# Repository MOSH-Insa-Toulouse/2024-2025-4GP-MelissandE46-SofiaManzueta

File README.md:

# 2024-2025-4GP-MelissandE46-SofiaManzueta

# Projet Capteur

## Sommaire 
*  [Objectifs de ce projet](#objectifs-de-ce-projet)
*  [Déroulé du projet](#diagramme-du-projet)
*  [Simulation du capteur graphite sur LTSpice](#simulation-du-capteur-graphite-sur-ltspice)
*  [Shield PCB sur Kicad](#shield-pcb-sur-kicad)
*  [Code Arduino](#code-arduino)
*  [App Android](#app-android)
*  [La Datasheet](#la-datasheet)

## Objectifs de ce projet

<details>
<summary>  Création d'un capteur de contrainte en graphite  </summary>
   Nous allons utiliser les traces de crayon sur du papier comme une jauge de contrainte pour détecter les déformations en compression et en traction.<br/>
   Les mines de crayon standard sont composées de fines particules de graphite liées entre elles par des liants argileux. Lorsqu'on utilise un crayon, le frottement entre la mine et le papier entraîne le frottement de particules de graphite qui adhèrent aux fibres du papier. Ces traces de crayon peuvent être considérées comme de minces films conducteurs constitués de réseau de particules de graphite percolées sur le papier qui peuvent prendre des formes et des motifs arbitraires. L'expansion et la contraction de ce réseau de particules de graphite, induites par des contraintes mécaniques ou des interactions chimiques, devraient grandement affecter la qualité des contacts interparticulaires et donc le conductivité électrique globale. Il est important de noter que les mines de crayon plus dures contiennent une proportion plus élevée de liants argileux, alors que les mines plus molles contiennent une proportion plus grande de particules de graphite. Ces dernières permettent d'obtenir une résistance de base plus faible qu'avec les mines plus dures. Il a été observé que les variations de résistance moyennes étaient linéairement liées aux amplitudes moyennes de déflexion, avec des écarts d'environ 1%.<br/>
En utilisant la théorie de la percolation, la conductance totale G_{tot} d'un réseau de conducteurs hautement désordonné est :<br/>
   $$G_{tot}=G_0e^{-\xi_c}$$, ici $$\xi_c$$ est la valeur de $$\xi$$ au seuil de percolation qui est le point où un cluster connecté infiniment grand commence à émerger lorsque des paires de nanoparticules voisines choisie au hasard sont connectées par des conducteurs dans un ordre décroissant de valeurs de G<br/>
   If $$-\delta\lambda/2\leq\delta\lambda/2$$,<br/>
   $$\xi_c= \left( {\frac{2f_c\delta\lambda\delta\epsilon}{1-f_v}} \right)^{1/2}+\delta_M-\delta\lambda/2+\epsilon_M-\delta\epsilon/2$$ <br/>
   If $$\delta\lambda/2-\delta\epsilon/2\leq\delta\epsilon/2-\delta\lambda/2$$, <br/>
   $$\xi_c=\lambda_M+\epsilon_M-\left( \frac{1}{2}-\frac{f_c}{1-f_v} \right)\delta\epsilon$$<br/>
   *  $$f_c$$ est la fraction des conducteurs<br/>
   *  $$f_v$$ est la fraction de vide<br/>
   *  $$\lambda_M=L_M\beta$$ et $$E_M=E_{CM}/kT$$ sont les valeurs moyennes des distributions, avec $$L_M$$ l'espace moyen (hors vide) séparant les nanoparticules voisines et $$E_{CM}$$ l'énergie coulombienne de charge moyenne<br/>
   *  $$\delta\lambda$$ et $$\delta\epsilon$$ sont les largeurs des distributions
  
</details>

<details>
<summary>  Réalisation d'un shield PCB pour Arduino UNO  </summary>
   Nous avons créer un shield PCB afin de relier à l'arduino UNO :<br/>  
        *  Un écran OLED  <br/>
        *  Un potentiomètre digital en SPI   <br/>
        *  Un amplificateur transimpédance, lui-même relié au capteur graphite décrit plus haut et au potentiomètre digital  <br/>
        *  Un module Bluetooth  <br/>
        *  Un flex sensor  <br/>
        *  Un encodeur rotatoir auquel on ajoute un déparasite (une capacité entre la clock et le ground)   <br/><br/>

</details>

<details>
<summary>  Création d'un code Arduino  </summary>
Le code crée à l'occasion de ce projet permet de se déplacer dans un menu à l'aide de l'encodeur rotatoire et accéder à différentes fonctions telles que :<br/>
   -La fonction Capteur qui mesure la résistance du capteur graphite, l'affiche sur l'écran OLED et la transmet par bluetooth<br/>
   -La fonction Flex qui mesure la résistance du flex sensor et l'affiche sur l'écran OLED<br/>
   -La fonction Mesure continue qui indique à l'utilisateur la marche à suivre pour réaliser une mesure en continue, que ce soit pour le flex sensor ou le capteur graphite * <br/>
   -La fonction Informations qui renvoie l'utilisateur vers l'application pour Android pour obtenir plus d'informations, l'écran OLED étant très limité<br/>
   -La fonction Creatrices qui indique tout simplement par qui a été réalisé ce projet<br/>

   *Un fil reliant la pin Switch de l'encodeur rotatoire avec le flex sensor a été ajouté. Le but principal est d'agir comme une résistance pull-up pour pouvoir utiliser le bouton switch plus simplement. Cependant, il permet également d'utiliser le flex sensor comme un bouton. En maintenant le flex sensor en compression, on obtient donc des mesures en continue.
   
</details>

<details>
<summary>  Élaboration d'une app Android  </summary>
  Une application a été créée à l'aide de MIT App Inventor (https://appinventor.mit.edu/). Celle-ci permet d'accéder aux mesures réalisées par le capteur graphite, de les afficher dans un graphe et de récupérer ses valeurs dans un fichier. Elle permet également d'obtenir de plus amples informations sur le contexte de ce projet lorsqu'on arrive sur l'écran Informations. Les photos de la partie Designers (ce qui est vu par l'utilisateur) et la partie Blocks (le code derrière l'application) sont disponibles dans le dossier Application Android.
</details>

<details>
<summary>  Rédaction datasheet  </summary>
  Les données de la datasheet proviennent des mesures réalisées avec le code Arduino sur le circuit présenté précédemment. Pour les mines 6B à HB, nous avons mesurer la résistance du capteur graphite pour différentes déformations en tension et en compression. Pour ces déformations, nous avons utilisé des cylindres avec des diamètres de 2cm, 2.5cm, 3cm, 3.5cm, 4cm, 4.5cm et 5cm. Cela nous donne donc des déformations respectivement de 0.1, 0.08, 0.067, 0.057, 0.05, 0.044, 0.04 puisque nous avons mesuré l'épaisseur du capteur e = 0.2cm et que $$\epsilon = \frac{e}{D}$$. On obtient ainsi les courbes caractéristiques suivantes. 

Comme on s'y attendait, en cas de compression, la résistance du capteur graphite diminue lorsque la déformation $$\epsilon$$ augmente. A l'inverse, en cas de tension, la résistance du capteur graphite augmente en fonction de la déformation $$\epsilon$$. Pour ces deux cas de figure, nous pouvons observer que la pente de la courbe est dépendante de la mine utilisée. En effet, la variation relative de résistance est plus élevée pour les mines plus dures, comme cela est décrit dans l'article Pencil Drawn Strain Gauges and Chemiresistors on Paper de Cheng-Wei Lin, Zhibo Zhao, Jaemyung Kim et Jiaxing Huang.

Les résultats du capteur graphite peuvent également être comparés à ceux obtenus avec un flex sensor commercial (celui-ci ne peut être utilisé qu'en tension). Tout d'abord, on peut remarquer que les mesures du flex sensor sont bien plus régulières que celles du capteur graphite. De plus, ses variations relatives de résistance sont plus élevées. Il est important de noter que les mesures du capteur graphite, que ce soit en tension ou en compression, sont peu fiables et dépendent en grande partie du reste du matériel utilisé. En effet, d'une mesure à une autre dans des conditions similaires les résultats du capteur peuvent grandement varier. De plus, pour obtenir des résultats cohérents, nous avons dû emprunter les pinces crocodiles d'un autre groupe, sinon peu importe la déformation et la mine utilisées la résistance mesurée était infinie.<br/><br/>
Nous pouvons donc en conclure que le capteur présenté à l'avantage d'être simple, sobre et abordable. Cependant, ses performances sont encore très éloignées de celles d'un flex sensor commercial. De plus, nous avons remarqué que nous devions régulièrement remettre du graphite sur le capteur et le remplacer par un nouveau après l'avoir utilisé en compression et en tension. Cela va donc à l'encontre du principe de la low-tech.

</details>

## Déroulé du projet 

<details>
<summary>  Etapes du projet :  </summary>
  
  - [x] Attribution des inputs de l'arduino aux différents composants
  - [X] Electronique Analogique
  - [x] Schématique et routage KiCad  
  - [x] Impression du circuit
  - [x] Percage
  - [x] Montage du circuit
  - [x] Code Arduino
  - [x] App Android
  - [x] Création du banc de test
  - [x] Création de la datasheet
</details>

## Simulation du capteur graphite sur LTSpice 
* Création d'un capteur de contrainte en graphite
<br/>
Sur le schéma ci-dessus, la partie supérieure à gauche sert à modéliser le capteur graphite.<br/>
C2 filtre le bruit d'alimentation.<br/>
C3 et R5 sont un filtre de sortie.<br/>
C4 et R4 sont un filtre actif.<br/>
R3 correspond au potentiomètre, il permettra donc un changement de calibre.<br/>
C1 et R2 sont un filtre pour le bruit en courant.<br/>
R1 et C1 sont un filtre pour les bruits en tension.<br/>
V3 et C5 simule du bruit.<br/>

## Shield PCB sur Kicad

Des images du schematic, modèle 3D et PCB finale entre autres sont disponibles [ici](https://github.com/MOSH-Insa-Toulouse/2024-2025-4GP-MelissandE46-SofiaManzueta/tree/main/Kidad%20-%20Projet%20capteur)

## Code Arduino

Le code se trouve ici avec une photo du menu déroulant : [Code Arduino](https://github.com/MOSH-Insa-Toulouse/2024-2025-4GP-MelissandE46-SofiaManzueta/tree/main/Code%20Arduino/Final_Code4.0)

## App Android

[Images faces avants et faces arrières de l'application Android](https://github.com/MOSH-Insa-Toulouse/2024-2025-4GP-MelissandE46-SofiaManzueta/tree/main/Application%20Android)

## La Datasheet

[La Datasheet](https://github.com/MOSH-Insa-Toulouse/2024-2025-4GP-MelissandE46-SofiaManzueta/tree/main/Datasheet)

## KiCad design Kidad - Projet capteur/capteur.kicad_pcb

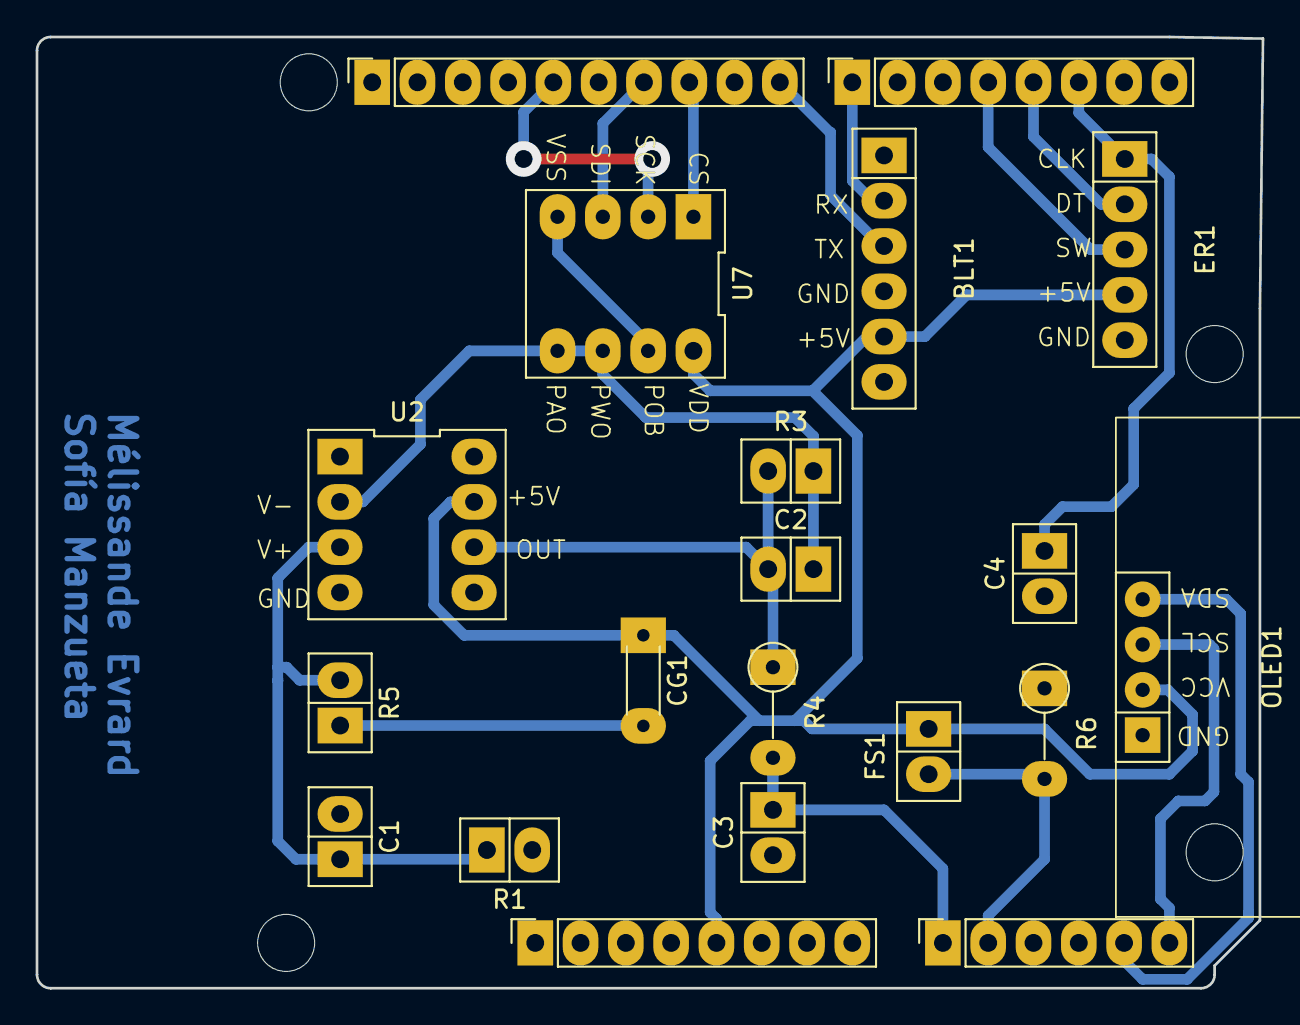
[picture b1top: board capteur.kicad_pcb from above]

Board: 2 copper layers, 68.8 x 53.3 mm, 24 parts (0 on the bottom side), 18 nets.

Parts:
BLT1: Bluetooth
C1, C3, C4: 100n; C
C2: 1u; C
CG1: R_Axial_DIN0204_L3.6mm_D1.6mm_P5.08mm_Horizontal
ER1: Encodeur rotatif
FS1: FlexSensor
J1: Power; PinSocket_1x08_P2.54mm_Vertical
J2: Digital/PWM; PinSocket_1x10_P2.54mm_Vertical
J3: Analog; PinSocket_1x06_P2.54mm_Vertical
J4: Digital/PWM; PinSocket_1x08_P2.54mm_Vertical
MH1, MH2, MH3, MH4: MountingHole_3.2mm
OLED1: OLED1306
R1, R3: 100k; R
R4: 1k; R_Axial_DIN0207_L6.3mm_D2.5mm_P5.08mm_Vertical
R5: 10k; R
R6: 47k; R_Axial_DIN0207_L6.3mm_D2.5mm_P5.08mm_Vertical
U2: LTC1050; AOP_LTC1050
U7: MCP41050; Potentiomètre

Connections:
+5V: BLT1.5 (+5V), CG1.1 (+5V), ER1.4 (+5V), FS1.1, J1.5, OLED1.2 (VCC), U2.7 (V+), U7.8 (VDD)
ADC: C3.1, J3.1, R4.2
CLK: C4.1, ER1.1 (CLK), J4.6
CS: J2.8, U7.1 (~CS)
DT: ER1.2 (DT), J4.5
FS: FS1.2, J3.2, R6.2
GND: BLT1.4 (GND), C1.2, C3.2, C4.2, ER1.5 (GND), J1.6, J1.7, J2.4, OLED1.1 (GND), R1.2, R6.1, U2.4 (V-), U7.4 (VSS), U7.7 (POB)
unnamed: C2.2, R3.2, R4.1, U2.6
unnamed: CG1.2 (OUT), R5.1
unnamed: C1.1, R1.1, R5.2, U2.3 (+)
R2: C2.1, R3.1, U2.2 (-), U7.5 (PAO), U7.6 (PWO)
RX: BLT1.2 (RxD), J4.1
SCK: J2.5, U7.2 (SCK)
SCL: J3.6, OLED1.3 (SCL)
SDA: J3.5, OLED1.4 (SDA)
SDI: J2.7, U7.3 (SDI)
SW: ER1.3 (SW), J4.4
TX: BLT1.3 (TxD), J2.10

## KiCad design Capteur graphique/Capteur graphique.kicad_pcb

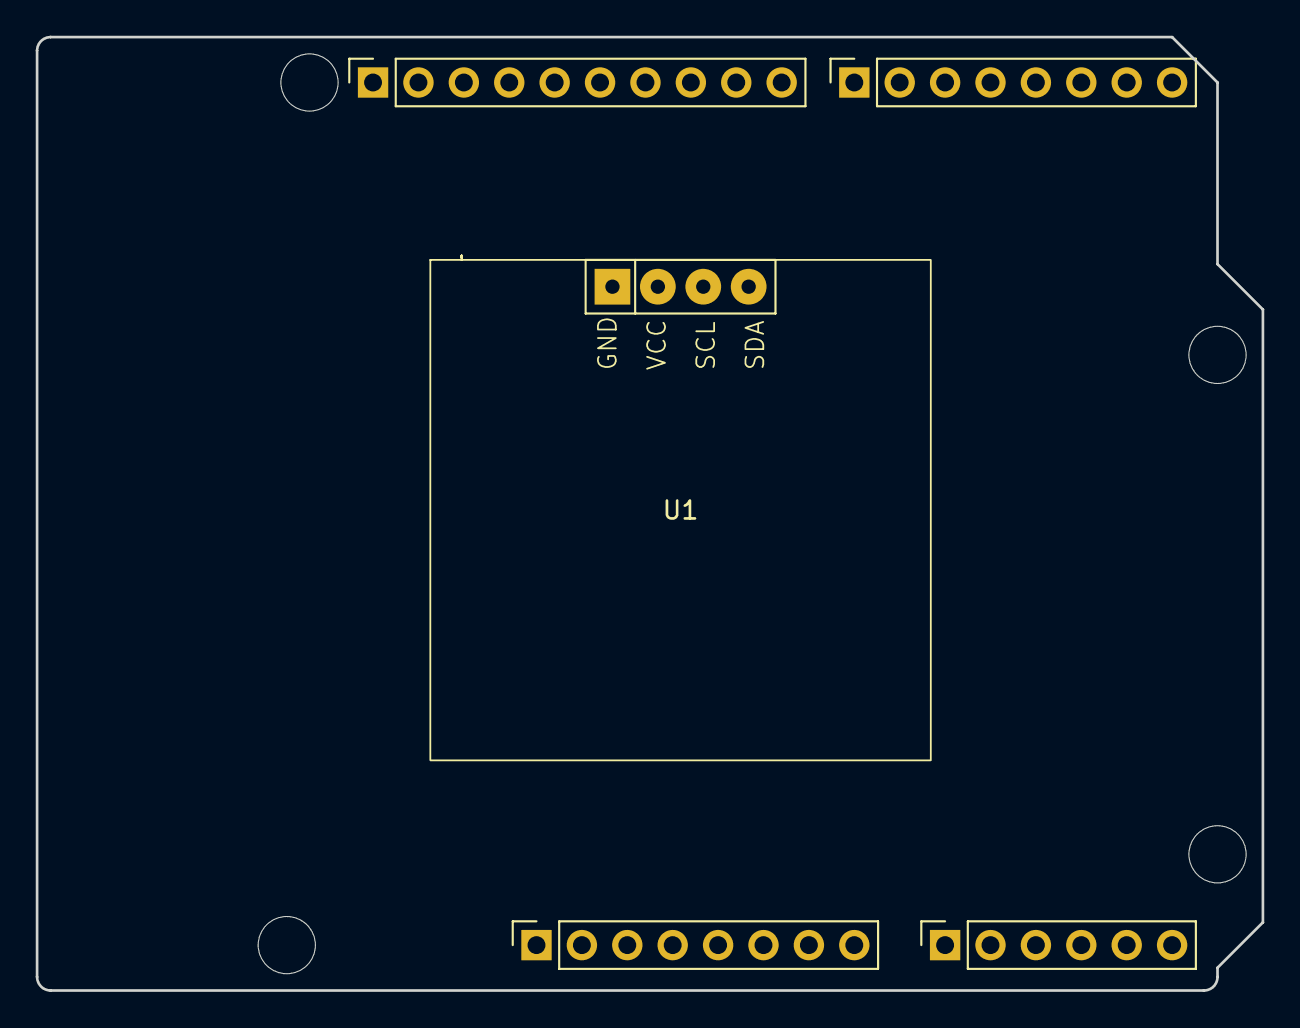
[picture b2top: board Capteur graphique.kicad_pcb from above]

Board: 2 copper layers, 68.6 x 53.3 mm, 9 parts (0 on the bottom side), 3 nets, no tracks yet.

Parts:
J1: Power; PinSocket_1x08_P2.54mm_Vertical
J2: Digital/PWM; PinSocket_1x10_P2.54mm_Vertical
J3: Analog; PinSocket_1x06_P2.54mm_Vertical
J4: Digital/PWM; PinSocket_1x08_P2.54mm_Vertical
MH1, MH2, MH3, MH4: MountingHole_3.2mm
U1: OLED 1306

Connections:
/SCL/A5: J2.1, J3.6
/SDA/A4: J2.2, J3.5
GND: J1.6, J1.7, J2.4

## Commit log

2025-02-21 essaie
2025-02-21 Modif de ligne 5 du fichier README
2025-02-21 Ma contribution qui a durée 4h
2025-02-21 Correction du fichier
2025-02-21 change
2025-03-16 update read
2025-03-18 Update README.md
    Description shield et capteur graphite ajoutée
2025-03-18 Update README.md
    formules mathématiques ajoutées
2025-05-20 Add files via upload
    Add of pictures from Kicad
2025-05-20 Add files via upload
    Add of pictures from the Android app
2025-05-20 Add files via upload
    Add of Arduino code
